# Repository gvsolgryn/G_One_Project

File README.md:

# 두원공과대학교 스마트 IT 캡스톤 디자인

# 1. G.One 프로젝트에 대하여...

이 프로젝트는 게임을 하는 도중 전등을 제어 하거나 멀티탭같은 전자기기를 제어 하면 편할 것 같다는 생각을 하여 진행한 프로젝트입니다.

## Software List

1. G_One_HID_Listener / G_One_WPF (Windows 용 프로그램)
2. G_One_Xamarin (Android/iOS 어플리케이션)
3. G_One_Flask (웹서버)

## Hardware & Firmware List

1. G_One_AutoCad (3D 프린터용 모델링)
2. G_One_Firmware (QMK펌웨어를 이용하여 만든 키보드 펌웨어)
3. G_One_IoT_Firmware (NodeMCU 에 적용시킬 펌웨어)
4. G_One_PCB (키보드 PCB)

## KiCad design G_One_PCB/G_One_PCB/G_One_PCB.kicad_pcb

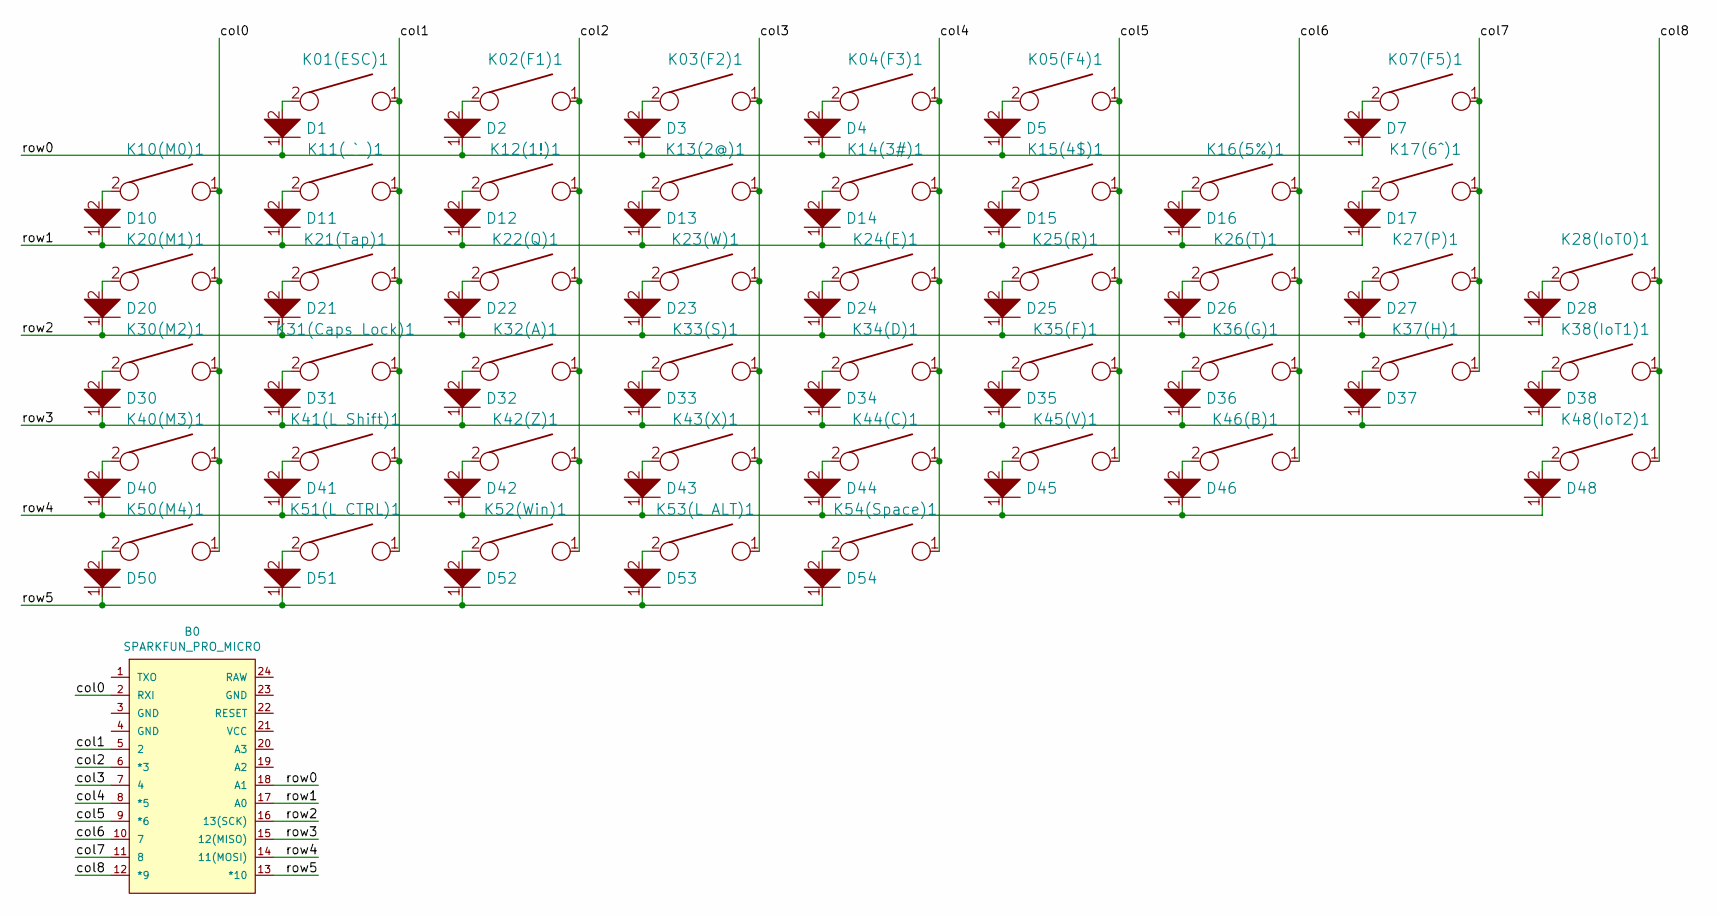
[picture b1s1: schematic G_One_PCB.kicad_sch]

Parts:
B0: SPARKFUN_PRO_MICRO
D1, D2, D3, D4, D5, D7, D10, D11, D12, D13, D14, D15, D16, D17, D20, D21, D22, D23, D24, D25, D26, D27, D28, D30, D31, D32, D33, D34, D35, D36, D37, D38, D40, D41, D42, D43, D44, D45, D46, D48, D50, D51, D52, D53, D54: D; D_SOD123_axial
K01(ESC)1, K02(F1)1, K03(F2)1, K04(F3)1, K05(F4)1, K07(F5)1, K10(M0)1, K11(_`_)1, K12(1!)1, K13(2@)1, K14(3#)1, K15(4$)1, K16(5%)1, K17(6^)1, K20(M1)1, K22(Q)1, K23(W)1, K24(E)1, K25(R)1, K26(T)1, K27(P)1, K28(IoT0)1, K30(M2)1, K32(A)1, K33(S)1, K34(D)1, K35(F)1, K36(G)1, K37(H)1, K38(IoT1)1, K40(M3)1, K42(Z)1, K43(X)1, K44(C)1, K45(V)1, K46(B)1, K48(IoT2)1, K50(M4)1: KEYSW; Mx_Alps_100
K21(Tap)1: KEYSW; Mx_Alps_150
K31(Caps_Lock)1: KEYSW; Mx_Alps_175
K41(L_Shift)1: KEYSW; Mx_Alps_225
K51(L_CTRL)1, K52(Win)1, K53(L_ALT)1: KEYSW; Mx_Alps_125
K54(Space)1: KEYSW; Mx_Alps_275

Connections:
/col0: B0.2 (RXI), K10(M0)1.1, K20(M1)1.1, K30(M2)1.1, K40(M3)1.1, K50(M4)1.1
/col1: B0.5 (2), K01(ESC)1.1, K11(_`_)1.1, K21(Tap)1.1, K31(Caps_Lock)1.1, K41(L_Shift)1.1, K51(L_CTRL)1.1
/col2: B0.6 (*3), K02(F1)1.1, K12(1!)1.1, K22(Q)1.1, K32(A)1.1, K42(Z)1.1, K52(Win)1.1
/col3: B0.7 (4), K03(F2)1.1, K13(2@)1.1, K23(W)1.1, K33(S)1.1, K43(X)1.1, K53(L_ALT)1.1
/col4: B0.8 (*5), K04(F3)1.1, K14(3#)1.1, K24(E)1.1, K34(D)1.1, K44(C)1.1, K54(Space)1.1
/col5: B0.9 (*6), K05(F4)1.1, K15(4$)1.1, K25(R)1.1, K35(F)1.1, K45(V)1.1
/col6: B0.10 (7), K16(5%)1.1, K26(T)1.1, K36(G)1.1, K46(B)1.1
/col7: B0.11 (8), K07(F5)1.1, K17(6^)1.1, K27(P)1.1, K37(H)1.1
/col8: B0.12 (*9), K28(IoT0)1.1, K38(IoT1)1.1, K48(IoT2)1.1
/row0: B0.18 (A1), D1.1, D2.1, D3.1, D4.1, D5.1, D7.1
/row1: B0.17 (A0), D10.1, D11.1, D12.1, D13.1, D14.1, D15.1, D16.1, D17.1
/row2: B0.16 (13(SCK)), D20.1, D21.1, D22.1, D23.1, D24.1, D25.1, D26.1, D27.1, D28.1
/row3: B0.15 (12(MISO)), D30.1, D31.1, D32.1, D33.1, D34.1, D35.1, D36.1, D37.1, D38.1
/row4: B0.14 (11(MOSI)), D40.1, D41.1, D42.1, D43.1, D44.1, D45.1, D46.1, D48.1
/row5: B0.13 (*10), D50.1, D51.1, D52.1, D53.1, D54.1
unnamed: D1.2, K01(ESC)1.2
unnamed: D2.2, K02(F1)1.2
unnamed: D3.2, K03(F2)1.2
unnamed: D4.2, K04(F3)1.2
unnamed: D5.2, K05(F4)1.2
unnamed: D7.2, K07(F5)1.2
unnamed: D10.2, K10(M0)1.2
unnamed: D11.2, K11(_`_)1.2
unnamed: D12.2, K12(1!)1.2
unnamed: D13.2, K13(2@)1.2
unnamed: D14.2, K14(3#)1.2
unnamed: D15.2, K15(4$)1.2
unnamed: D16.2, K16(5%)1.2
unnamed: D17.2, K17(6^)1.2
unnamed: D20.2, K20(M1)1.2
unnamed: D21.2, K21(Tap)1.2
unnamed: D22.2, K22(Q)1.2
unnamed: D23.2, K23(W)1.2
unnamed: D24.2, K24(E)1.2
unnamed: D25.2, K25(R)1.2
unnamed: D26.2, K26(T)1.2
unnamed: D27.2, K27(P)1.2
unnamed: D28.2, K28(IoT0)1.2
unnamed: D30.2, K30(M2)1.2
unnamed: D31.2, K31(Caps_Lock)1.2
unnamed: D32.2, K32(A)1.2
unnamed: D33.2, K33(S)1.2
unnamed: D34.2, K34(D)1.2
unnamed: D35.2, K35(F)1.2
unnamed: D36.2, K36(G)1.2
unnamed: D37.2, K37(H)1.2
unnamed: D38.2, K38(IoT1)1.2
unnamed: D40.2, K40(M3)1.2
unnamed: D41.2, K41(L_Shift)1.2
unnamed: D42.2, K42(Z)1.2
unnamed: D43.2, K43(X)1.2
unnamed: D44.2, K44(C)1.2
unnamed: D45.2, K45(V)1.2
unnamed: D46.2, K46(B)1.2
unnamed: D48.2, K48(IoT2)1.2
unnamed: D50.2, K50(M4)1.2
unnamed: D51.2, K51(L_CTRL)1.2
unnamed: D52.2, K52(Win)1.2
unnamed: D53.2, K53(L_ALT)1.2
unnamed: D54.2, K54(Space)1.2

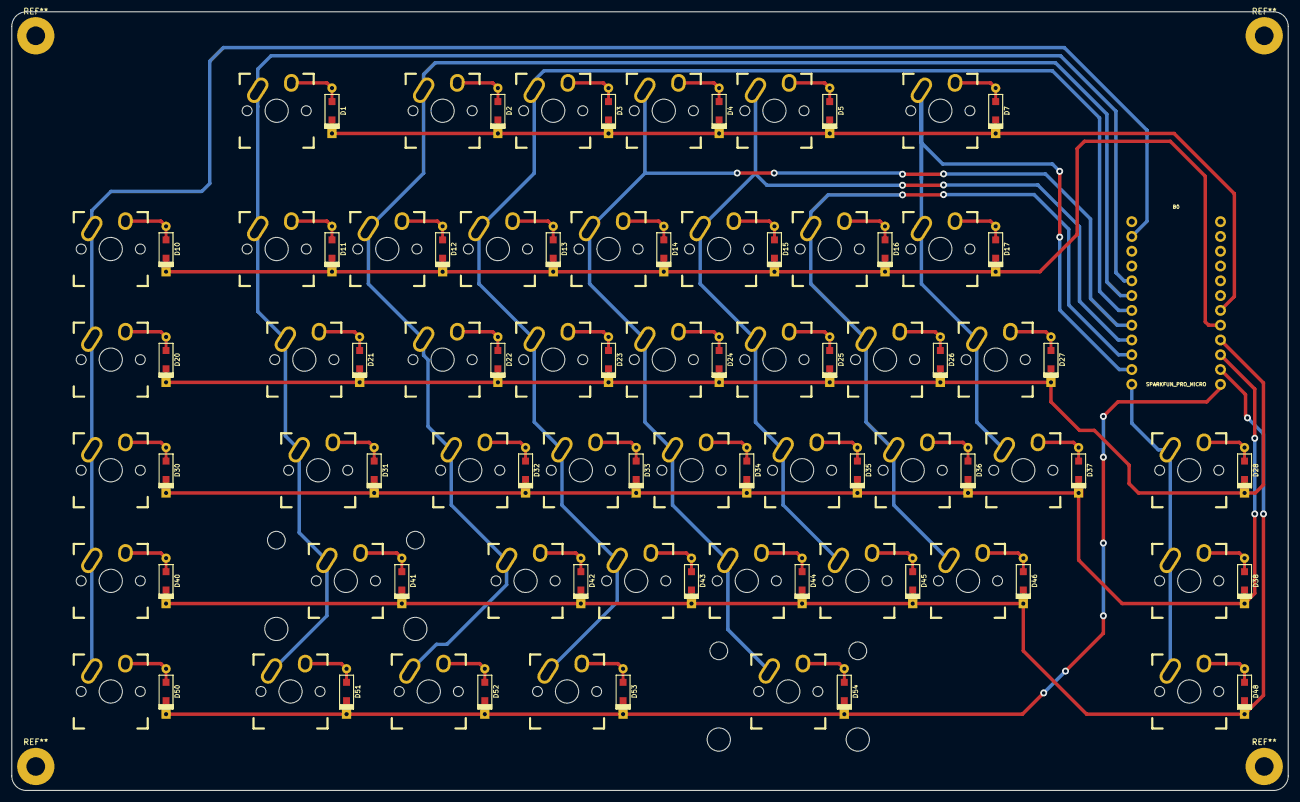
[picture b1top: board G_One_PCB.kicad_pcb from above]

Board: 2 copper layers, 219.2 x 133.8 mm, 91 parts (0 on the bottom side), 60 nets.

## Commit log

2021-08-16 Git 초기 설정
2021-08-16 PCB 기판에 SW 배치 완료(위치 수정 필요)
2021-08-22 gitignore 설정 변경
2021-08-22 app.config 세팅 변경(테스트 필요)
2021-08-23 서버 초기화 작업을 위해서 임시로 개인정보가 올라간 파일들도 업로드 합니다.
2021-08-26 디버그 실시
2021-08-29 db서버 복원 완료
2021-08-29 DB 백업본 sql 업로드
2021-08-30 main 화면에서 run.py를 통해 Flask 서버를 작동 시킬 수 있게 파일을 추가
2021-08-30 Flask 서버를 더욱 간단하게 실행 시킬 수 있도록 run.py 생성 및 작동 할 수 있게 모듈 import 방식 수정
2021-08-30 bootstrap5 에 맞춰서 웹페이지 디자인 변경 및 구조 변경중
2021-09-14 자잘한 것들 수정
2021-09-14 db모듈에 close 추가, mqtt host 변경, 테스트 환경 구성
2021-09-14 Add QMK Firmware
2021-09-14 Add led Adjust range bar / db sql update
2021-09-14 21/09/15 db sql backup
2021-09-20 간단한것 변경
2021-09-20 IoT 기기 추가 기능 추가
2021-09-25 소스코드 수정
2021-09-26 자마린 추가 HID 인식 안되던거 수정
2021-09-26 DB 연동기능 추가/HID Report 관련 오류 수정
2021-09-26 flask server code edit
2021-10-03 Add Flask Sensor_Delete method
2021-10-03 C# : Add AddDeviceForm and dbmodule
2021-10-04 Add DB_Module
2021-10-05 Add stl file
2021-10-05 이제 웹페이지에서 LED 밝기 조정이 가능합니다
2021-10-06 드디어 OnReport 버그 수정 완료!!
2021-10-11 G.One 키보드 PCB 디자인 완료 / 거버 파일 생성
2021-10-12 DB Module 생성
2021-10-12 DB Module 추가 및 이미지 버튼 작동 가능하게 업데이트
2021-10-12 필요없는 프로젝트 제거 및 HID 기능 추가
2021-10-12 프로그램 최소화 활성화 / 기기 추가&기기 삭제 기능 구현 완료
2021-10-12 gitignore 재설정
2021-10-12 Revert "Delete ico.ico"
    This reverts commit 8f7826f8e6d6b1d0dc7b42693dfdd6f3dabfd97d.
2021-10-12 Add test keyboard firmware
2021-10-13 TestKeyboard Firmware 수정
2021-10-13 pcb 수정
2021-10-13 PCB 제작 완료 및 거버 파일 생성
2021-10-17 Create G_One_HID_WPF
2021-10-17 기기 추가 메소드 변경
2021-10-18 db 연동 및 기능 추가
2021-10-19 Add DeviceControl Module / MQTT Module
2021-10-24 수정중...
2021-10-26 펌웨어 업데이트
2021-10-26 WPF 에서 LOG 창 구현 완료
2021-11-07 임시적으로 밝기제어 탭 수정
2021-11-10 LED 밝기 제어가 가능한 제품에 슬라이더 표시가 됨
2021-11-10 소스코드 버전 관리 중 오류가 있었던것 수정
2021-11-10 자마린 추가
2021-11-10 자마린 수정중
2021-11-10 자마린 수정중
    Former-commit-id: c1f5aa66b0a0dfae6cfa9de40621bf9d4667ca85
2021-11-10 이그노어 수정
2021-11-10 이그노어 수정
    Former-commit-id: 6b145a41017bd2d4802a84bc5366d54015b70842
2021-11-10 Delete G_One_Xamarin/G_One_Xamarin/G_One_Xamarin.Android/bin/Debug directory
    Former-commit-id: ad5df44b03fe113e437a7f921be0641d0c40214f
2021-11-10 자마린 빌드 테스트
2021-11-10 자마린 빌드 테스트
    Former-commit-id: 942c25e97a47e3aba4543aab2a96a14d22867a3c
2021-11-10 자마린 빌드 테스트
    Former-commit-id: e515bc427960ba233b8f03b313aa86c8ee4984aa
2021-11-10 .
    Former-commit-id: 492b17c7153cc1042595e0eb0948f8ccc5f6bc21
2021-11-10 .
    Former-commit-id: 7866f6840f6a9f440c1426020d1166fb6881de42
2021-11-10 .
    Former-commit-id: cf96334aae347f28c29f7481c660b6efc1dff682
2021-11-10 Delete G_One_Xamarin/G_One_Xamarin/G_One_Xamarin.iOS/obj directory
    Former-commit-id: 9a356fe2ac57ab38a053e2c3a87cbfff404090f2
2021-11-10 Delete G_One_Xamarin/G_One_Xamarin/G_One_Xamarin.iOS/bin directory
    Former-commit-id: 0c1d95b41a65ce122f8bc04d141fb5ecee61a937
2021-11-10 Delete G_One_Xamarin/G_One_Xamarin/G_One_Xamarin/obj directory
    Former-commit-id: 4f643c41003c09e67f8010a378fc10711a2a7286
2021-11-10 Delete G_One_Xamarin/G_One_Xamarin/G_One_Xamarin.UWP directory
    Former-commit-id: 856d2480cac1516b96bdac9356aeaaab5c1a9ae6
2021-11-10 자마린 버그때문에 일단 삭제
2021-11-10 자마린 버그때문에 일단 삭제
    Former-commit-id: d774208e42cc67cda8ece4d211e14708fc673c30
2021-11-10 Update .gitignore
    Former-commit-id: 3ef60fb0d43f70f7e84af26d8e71896fe4a22b04
2021-11-10 Update .gitignore
    Former-commit-id: 210f02990984b38ca022470b0cede69ce1542645
2021-11-14 G_One_Xamarin 추가(gitignore 과 함께 추가됨)
2021-11-14 G_One_Xamarin 추가(gitignore 과 함께 추가됨)
    Former-commit-id: 8aece23f46779926377d0b378e7b3119b166d5e8
2021-11-14 Update DevicePanel.xaml
    Former-commit-id: 2a27d3141c0e3cb4fed8de0e8d943aa39577c93a
2021-11-14 DB_Module 예외 처리 수정 DevicePanel 수정중
    Former-commit-id: bae86d6d72cbc33081aa7738de69ecc72376b6d8
2021-11-14 DB_Module 예외 처리 수정 DevicePanel 수정중
2021-11-14 당겨서 새로고침 구현
2021-11-14 당겨서 새로고침 구현
    Former-commit-id: da33a985607edd1969eea8720de251f935fbc92b
2021-11-14 임시적으로 데이터베이스와 연동되도록 설정
2021-11-14 임시적으로 데이터베이스와 연동되도록 설정
    Former-commit-id: 764870c69bb1f5d8efd3ca9fcb7cee25fbf1802a
2021-11-14 DB 연동 및 기능 추가
    Former-commit-id: 09e5ff759ef67f149e23049abd75256c04b526bf
2021-11-15 메인 페이지를 네비게이션 페이지로 생성
2021-11-15 메인 페이지를 네비게이션 페이지로 생성
    Former-commit-id: f960536426c08bea6f12fd2d4d661ffd39bc897b
2021-11-15 디바이스 패널 이름 수정
2021-11-15 디바이스 패널 이름 수정
    Former-commit-id: a840fef04dd9ff89109bc616bd7802bbf84904c9
2021-11-15 모달 페이지 추가
2021-11-15 모달 페이지 추가
    Former-commit-id: d15e60ca188fbc6957fedcb5f9fbc19f4ab4a4a9
2021-11-16 기기 삭제 기능 추가
2021-11-16 기기 삭제 기능 추가
    Former-commit-id: 12fa21b1260b44b1dbb81f49019f92f64e7135e3
2021-11-16 기기 추가 기능 추가
2021-11-16 기기 추가 기능 추가
    Former-commit-id: f4399c4ec7341c3d4453ad42d283dd0da2712d95
2021-11-16 모듈 약간 변경
    Former-commit-id: 01c01fb91680e7196ad2370a4709816324fee5af
2021-11-16 모듈 약간 변경
2021-11-16 디바이스 컨트롤 모듈 수정
2021-11-16 디바이스 컨트롤 모듈 수정
    Former-commit-id: c47f444de8c9d53100f7bc6b7a9a60aca4580547
2021-11-16 패널 수정
2021-11-16 패널 수정
    Former-commit-id: 3c691d36b1ed7def018292979d306e559a943b72
2021-11-16 임베디드 이미지 바인딩 변경
    Former-commit-id: 373221331ee5906429d04a7c4ad0ac35048db273
2021-11-16 임베디드 이미지 바인딩 변경
2021-11-16 Add MQTT Library
    Former-commit-id: 888cc7b3e8932aa47ebe70a46a8045e205cb38e5
2021-11-16 Add MQTT Library
2021-11-16 ADD Mqtt Connect
    Former-commit-id: a84d02b873612726ff1154b28d57068dc66ee06f
2021-11-16 ADD Mqtt Connect
2021-11-17 최대 안드로이드 버전 12로 업데이트
2021-11-17 최대 안드로이드 버전 12로 업데이트
    Former-commit-id: e870813bacbaabd933d4587dd19aea58bcd326c4
2021-11-17 밝기 제어 추가
2021-11-17 밝기 제어 추가
    Former-commit-id: 9cf6086f75e0c0437f627cf97a90c5a7b7a594e1
2021-11-17 밝기 제어 추가
    Former-commit-id: 355de8124a23761893a5f01158dae2aa506e0bb3
2021-11-17 아이콘 변경
2021-11-17 아이콘 변경
    Former-commit-id: ea0191e4c51953ce567cb45bfe4141a9d9512237
2021-11-17 아이콘 변경
    Former-commit-id: 32bc2713138767a14d1e9c0e87c523bb34b8f9b9
2021-11-17 서버 변경
2021-11-19 Xamarin 및 WPF 개발 중 변경 된 SQL 적용 및 중복 기기 추가 방지 기능 추가
2021-11-19 Xamarin 및 WPF 개발 중 변경 된 SQL 적용 및 중복 기기 추가 방지 기능 추가
    Former-commit-id: d13eee3383fda73b2df94ee2deac362ebb819371
2021-11-19 MQTT구독 기능 추가 테스트 하는중
2021-11-19 MQTT구독 기능 추가 테스트 하는중
    Former-commit-id: f5e9b649e5be4a8d8f25a011f2d9782d6b0c287e
2021-11-20 socket io 적용
    Former-commit-id: 736fa8aa5468b2068195ab8a2df8210a7e6b2e11
2021-11-20 socket io 적용
2021-11-21 .
    Former-commit-id: d6772171bbd31e3a28d79d165827851f913feb63
2021-11-21 .
    Former-commit-id: 9950be6e1c441e69d200ecfbea8772bb55acc3ce
2021-11-22 .
    Former-commit-id: 341f810092007d43968a1146b6617ce44a0c2980
2021-11-22 .
    Former-commit-id: ec8abffa5aa12847e5978ad0db15f6b078029e33
2021-11-22 급하게 수정
    Former-commit-id: fab66d39b372636e4a978d9555402d9de1d583f9
2021-11-22 급하게 수정
2021-11-22 test
2021-11-30 간단하게 수정 완료
2021-12-08 주석 작업중
2021-12-10 G.One WPF 주석 처리 완료
2021-12-11 안쓰는 파일 지우기
2021-12-11 G.One Xamarin 주석 작업
2023-04-27 필요없는 파일 삭제
2023-04-27 gitignore 수정 및 필요없는 파일 삭제
